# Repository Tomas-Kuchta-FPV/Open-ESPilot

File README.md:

# Open-ESPilot

This is a community-driven hardware project focused on creating an open and accessible Flight Controller (FC).   
The main focus is on being low-cost, availability, hackability and openness!  
That's why I've started this project to make an open-source and low-cost FC with the community.  

The target firmware is [ArduPilot](https://ardupilot.org/), which is a powerful open-source autopilot system.  

## Core Design Ideas
- *Dev board meets flight controller* hybrid
- Keep it budget-friendly
- Readily available components
- Hackability so you can hack on your features
- ❤️ Designed with care by and for the community

## What are the goals
The main one is a reference platform for devs and hackers. Then we can move to a product for the wider public.  

With the focus being on Hackability and Openness, there are endless possibilities for creativity!  
Here are a few ideas:
 - Prototyping and experimentation  
 - A low-cost alternative for those priced out of commercial FCs  
 - Teaching control theory and autonomous systems in schools  

## Why did I make it
I have a lot of experience with FPV drones running Betaflight.  

Then I started playing with the ESP32-based ArduPilot for almost three years. All of them were for a competition called Robotem Rovne.  
 - The first one is an autonomous rover which was breadboarded together. As with any other breadboard project, the wires were loose, they didn't make contact, and they were falling off.  
 - Then I made a second rover with an FC soldered on a proto board. Which worked wonderfully!  
 - Then I tried to make a PCB with a brushed motor controller. Not going to talk about this one. Didn't go as planned. :(  
 - After that, I've bought a SpeedyBee f405 WING FC and mounted it to an RC car. This is my Ardupilot learning platform.  

And now we are here. ...  
That was when I had the idea of making an ESP32 Flight Controller.  

## Future development
This is the first FC I made with the help of the community, so huge thanks to *everyone*. ♥️

### Ideas for future
 - modular system (eg, ELRS, GPS modules)
 - 30x30 FC for FPV drones. That's harder as there are plenty of great cheap FCs

## Project Status
**I have the PCB made, and now I need to order everything and test it!**
| PCB                                                                                                           | Render                                                                                          | Finished PCB                                                                                              |
| ------------------------------------------------------------------------------------------------------------- | ----------------------------------------------------------------------------------------------- | --------------------------------------------------------------------------------------------------------- |
|  |  |  |

### The Plan
- [x] Basic schematic and PCB layout
- [x] Selection of components is decided in [Issues](https://github.com/Tomas-Kuchta-FPV/Open-ESPilot/issues)
- [ ] Compare BOM cost to commercial FCs - going to figure it out when I have time.
- [ ] Complete code, documentation, and build guide

## Design Phases
1. **Planning & goal setting**✅
2. **Schematic design**✅
    - Start with core ESP32 + power
    - Add sensors and outputs
    - Evaluate BOM & gather feedback
3. **Community feedback loop**✅
4. **PCB layout**✅
5. **Prototype ordering**
6. **…And hopefully it works on the first try! 🤞**

## Firmware
We are now focusing on [ArduPilot ESP32 port](https://ardupilot.org/dev/docs/esp32-autopilot.html). They are making incredible work, and the project wouldn't exist without their hard work.  
I won't be able to write the code by myself, so huge props to the contributors! That's why I'm focusing on the HW.  
There are also possibilities for you to write your own code.  

## Contributing
We would love to hear feedback. We are open to everything, including issues, ideas and suggestions.  
That's why this project is Open Source.

## BOM
| Category      | Qty | Price (USD) | Description           | Link                                                                                                                                                           |
| ------------- | --- | ----------- | --------------------- | -------------------------------------------------------------------------------------------------------------------------------------------------------------- |
| PCB component | 1   | 0.9         | TMB12A05              | https://lcsc.com/product-detail/Buzzers_Huaneng-TMB12A05_C96093.html                                                                                           |
| PCB component | 14  | 0.46        | 100nF                 | https://lcsc.com/product-detail/Multilayer-Ceramic-Capacitors-MLCC-SMD-SMT_YAGEO-CC0805KRX7R9BB104_C49678.html                                                 |
| PCB component | 7   | 0.11        | 22uF                  | https://lcsc.com/product-detail/Multilayer-Ceramic-Capacitors-MLCC-SMD-SMT_Samsung-Electro-Mechanics-CL21A226MQQNNNE_C5674.html                                |
| PCB component | 1   | 0.53        | 1000uF                | https://lcsc.com/product-detail/Aluminum-Electrolytic-Capacitors-SMD_ROQANG-VT1A102M0810_C311227.html                                                          |
| PCB component | 1   | 0.57        | 1000uF (Leaded)       | https://lcsc.com/product-detail/Aluminum-Electrolytic-Capacitors-Leaded_AISHI-ERR1VM102G20OT_C398835.html                                                      |
| PCB component | 1   | 0.57        | SS34                  | https://lcsc.com/product-detail/Schottky-Diodes_MDD-Microdiode-Semiconductor-SS34_C8678.html                                                                   |
| PCB component | 2   | 0.98        | PDZVTR5.1B            | https://lcsc.com/product-detail/Zener-Diodes_ROHM-PDZVTR5-1B_C253499.html                                                                                      |
| PCB component | 1   | 0.84        | B5819W                | https://lcsc.com/product-detail/Schottky-Diodes_MDD-Microdiode-Semiconductor-B5819W_C64885.html                                                                |
| PCB component | 1   | 0.49        | WS2812B LED           | https://lcsc.com/product-detail/RGB-LEDs-Built-in-IC_XINGLIGHT-XL-5050RGBC-WS2812B_C2843785.html                                                               |
| PCB component | 1   | 0.22        | Ferrite Bead          | https://lcsc.com/product-detail/Ferrite-Beads_TDK-MPZ2012S101AT000_C15957.html                                                                                 |
| PCB component | 1   | 0.87        | USB-C Receptacle      | https://lcsc.com/product-detail/USB-Connectors_Korean-Hroparts-Elec-TYPE-C-31-M-12_C165948.html                                                                |
| PCB component | 1   | -           | MP1584 module (clone) | https://www.aliexpress.com/item/1005005870392716.html                                                                                                          |
| PCB component | 1   | -           | GY-91                 | https://www.aliexpress.com/item/32652866365.html                                                                                                               |
| PCB component | 1   | 0.6         | AO3401A               | https://lcsc.com/product-detail/MOSFETs_AOS-AO3401A_C15127.html                                                                                                |
| PCB component | 2   | 0.45        | BC847                 | https://lcsc.com/product-detail/Bipolar-BJT_Nexperia-BC847B-215_C57668.html                                                                                    |
| PCB component | 2   | 0.21        | 5.1k                  | https://lcsc.com/product-detail/Chip-Resistor-Surface-Mount_YAGEO-RC0805FR-075K1L_C84375.html                                                                  |
| PCB component | 2   | 0.19        | 10k                   | https://lcsc.com/product-detail/Chip-Resistor-Surface-Mount_YAGEO-RC0805FR-0710KL_C84376.html                                                                  |
| PCB component | 1   | 0.21        | 1k                    | https://lcsc.com/product-detail/Chip-Resistor-Surface-Mount_YAGEO-RC0805FR-075K1L_C84375.html                                                                  |
| PCB component | 5   | 0.19        | 10k                   | https://lcsc.com/product-detail/Chip-Resistor-Surface-Mount_YAGEO-RC0805FR-0710KL_C84376.html                                                                  |
| PCB component | 2   | 0.49        | 10R                   | https://lcsc.com/product-detail/Chip-Resistor-Surface-Mount_YAGEO-RC0805FR-0710RL_C96347.html                                                                  |
| PCB component | 1   | 0.41        | 0.5mΩ                 | https://lcsc.com/product-detail/Chip-Resistor-Surface-Mount_Viking-LR12FTDR0M50_C37635712.html                                                                 |
| PCB component | 4   | 0.19        | 1k                    | https://lcsc.com/product-detail/Chip-Resistor-Surface-Mount_YAGEO-RC0805FR-071KL_C95781.html                                                                   |
| PCB component | 2   | 0.63        | Push Button           | https://lcsc.com/product-detail/Tactile-Switches_ALPSALPINE-SKRKAEE020_C115357.html                                                                            |
| PCB component | 1   | 5.14        | ESP32-S3-WROOM-1-N8   | https://lcsc.com/product-detail/WiFi-Modules_ESPRESSIF-ESP32-S3-WROOM-1-N8_C2913198.html                                                                       |
| PCB component | 1   | 0.87        | AMS1117-3.3           | https://lcsc.com/product-detail/Voltage-Regulators-Linear-Low-Drop-Out-LDO-Regulators_Advanced-Monolithic-Systems-AMS1117-3-3_C6186.html                       |
| PCB component | 1   | 0.41        | AMS1117-3.3 (Alt)     | https://lcsc.com/product-detail/Voltage-Regulators-Linear-Low-Drop-Out-LDO-Regulators_Slkor-SLKORMICRO-Elec-AMS1117-3-3_C880752.html                           |
| PCB component | 1   | 2.84        | INA219                | https://lcsc.com/product-detail/Current-Sense-Amplifiers_TI-INA219AID_C1574856.html                                                                            |
| PCB component | 1   | 1.32        | Micro SD Card Slot    | https://lcsc.com/product-detail/SD-Card-Memory-Card-Connector_HRS-DM3AT-SF-PEJM5_C114218.html                                                                  |
| PCB component | 50  | 0.46        | Pin Header (5x10)     | https://lcsc.com/product-detail/Pin-Headers_BOOMELE-Boom-Precision-Elec-2-54-1-10P_C57369.html                                                                 |
| PCB component | -   | 13          | Shipping              | -                                                                                                                                                              |
| PCB           | -   | 10.72       | PCB cost              | https://cart.jlcpcb.com/quote?orderType=1&homeUploadNum=4c39875b107d460986bfa4ef1bf68f70&businessType=example&fileName=Open-ESPilot_50.6x71.1mm_for_JLCPCB.zip |
| **TOTAL**     | -   | 50.97       | -                     | -                                                                                                                                                              |

## Built With
- [ESP32](https://www.espressif.com/en/products/socs/esp32) – the core MCU
- [KiCad](https://kicad.org/) – for PCB design
- [ArduPilot](https://github.com/ArduPilot/ardupilot) – the autopilot software we're building for
- ❤️ Open source tools and community support
- ... and Love ❤️

## License
Hardware: [CERN-OHL-W](https://ohwr.org/cern_ohl_w_v2.txt)  

Firmware: Ardupilot  

## Thanks
Many thanks to the amazing people who make [Hack Club](https://hackclub.com/) possible.
Thanks to Hack Club for inspiring so many people. I don't know the numbers, but maybe around thousands.  
Most of them are probably going to get a career from it. Love your work! ❤️  

And big thanks to the ArduPilot community for keeping robotics and autonomy Open and hackable.

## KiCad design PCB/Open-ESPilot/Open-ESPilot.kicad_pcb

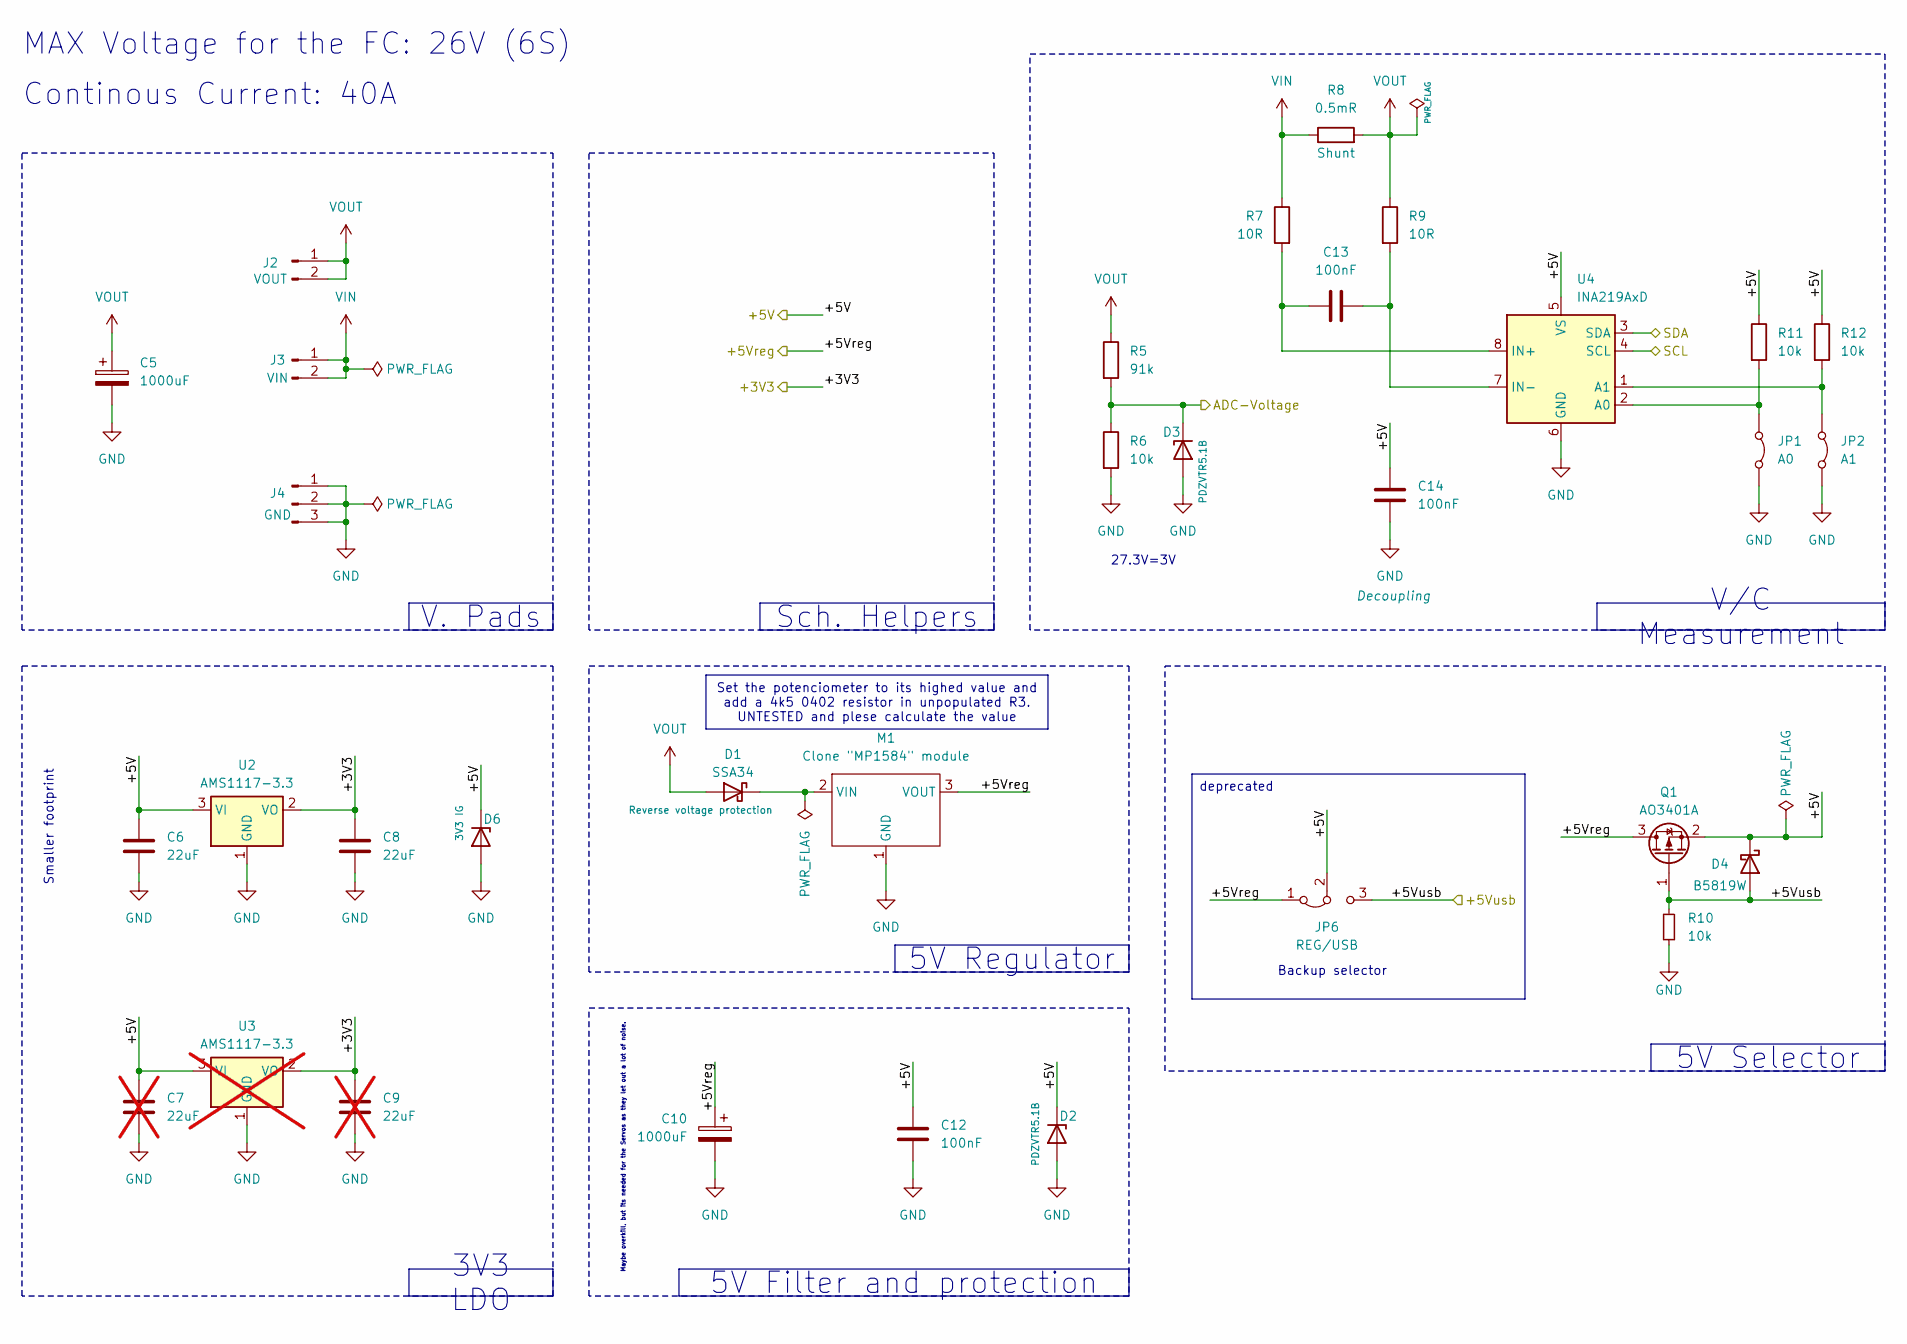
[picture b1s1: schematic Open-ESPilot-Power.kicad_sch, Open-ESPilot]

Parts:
C5: 1000uF; CP_Radial_D10.0mm_P5.00mm; LCSC C398835
C6, C8: 22uF; C_0805_2012Metric_Pad1.18x1.45mm_HandSolder; LCSC C5674
C7, C9: 22uF; C_0805_2012Metric_Pad1.18x1.45mm_HandSolder; LCSC C5674; not fitted
C10: 1000uF; CP_Elec_8x10; LCSC C311227
C12, C13, C14: 100nF; C_0805_2012Metric_Pad1.18x1.45mm_HandSolder; LCSC C49678
D1: SSA34; D_SMA; LCSC C8678
D2, D3: PDZVTR5.1B; D_SOD-128; LCSC C253499
D4: B5819W; D_SOD-123; LCSC C64885
D6: 3V3 IG; D_SOD-128
J2: VOUT; PP_02x
J3: VIN; PP_02x
J4: GND; PP_03x
JP1: A0; SolderJumper-2_P1.3mm_Bridged2Bar_RoundedPad1.0x1.5mm
JP2: A1; SolderJumper-2_P1.3mm_Bridged2Bar_RoundedPad1.0x1.5mm
JP6: REG/USB; SolderJumper-3_P1.3mm_Open_RoundedPad1.0x1.5mm
M1: Clone "MP1584" module; Clone _MP1584_ module
Q1: AO3401A; SOT-23; LCSC C15127
R5: 91k; R_0805_2012Metric_Pad1.20x1.40mm_HandSolder; LCSC C84375
R6, R10, R11, R12: 10k; R_0805_2012Metric_Pad1.20x1.40mm_HandSolder; LCSC C84376
R7, R9: 10R; R_0805_2012Metric_Pad1.20x1.40mm_HandSolder; LCSC C96347
R8: 0.5mR; R_2512_6332Metric_Pad1.40x3.35mm_HandSolder; LCSC C37635712
U2: AMS1117-3.3; SOT-89-3; LCSC C880752
U3: AMS1117-3.3; SOT-223-3_TabPin2; LCSC C6186; not fitted
U4: INA219AxD; SOIC-8_3.9x4.9mm_P1.27mm; LCSC C1574856

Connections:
+3V3: C8.1, C9.1, U2.2 (VO), U3.2 (VO); also elsewhere on the board
+5V: C6.1, C7.1, C12.1, C14.1, D2.1 (K), D4.1 (K), D6.1 (K), JP6.2 (C), Q1.2 (S), R11.1, R12.1, U2.3 (VI), U3.3 (VI), U4.5 (VS); also elsewhere on the board
+5Vreg: C10.1, JP6.1 (A), M1.3 (VOUT), Q1.3 (D); also elsewhere on the board
/Peripheral/ADC-Voltage: D3.1 (K), R5.2, R6.1; also elsewhere on the board
/Peripheral/SCL: U4.4 (SCL); also elsewhere on the board
/Peripheral/SDA: U4.3 (SDA); also elsewhere on the board
/Power/+5Vusb: D4.2 (A), JP6.3 (B), Q1.1 (G), R10.1; also elsewhere on the board
GND: C5.2, C6.2, C7.2, C8.2, C9.2, C10.2, C12.2, C14.2, D2.2 (A), D3.2 (A), D6.2 (A), J4.1, J4.2, J4.3, JP1.2 (B), JP2.2 (B), M1.1 (GND), R6.2, R10.2, U2.1 (GND), U3.1 (GND), U4.6 (GND); also elsewhere on the board
unnamed: D1.1 (K), M1.2 (VIN)
unnamed: JP1.1 (A), R11.2, U4.2 (A0)
unnamed: JP2.1 (A), R12.2, U4.1 (A1)
unnamed: C13.1, R7.2, U4.8 (IN+)
unnamed: C13.2, R9.2, U4.7 (IN-)
VIN: J3.1, J3.2, R7.1, R8.1
VOUT: C5.1, D1.2 (A), J2.1, J2.2, R5.1, R8.2, R9.1

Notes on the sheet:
Smaller footprint
MAX Voltage for the FC: 26V (6S)
Continous Current: 40A
Backup selector
Maybe overkill, but its needed for the Servos as they let out a lot of noise.
27.3V=3V
V. Pads
5V Regulator
Sch. Helpers
deprecated
3V3 LDO
V/C Measurement
5V Filter and protection
Set the potenciometer to its highed value and add a 4k5 0402 resistor in unpopulated R3. UNTESTED and plese calculate the value
5V Selector

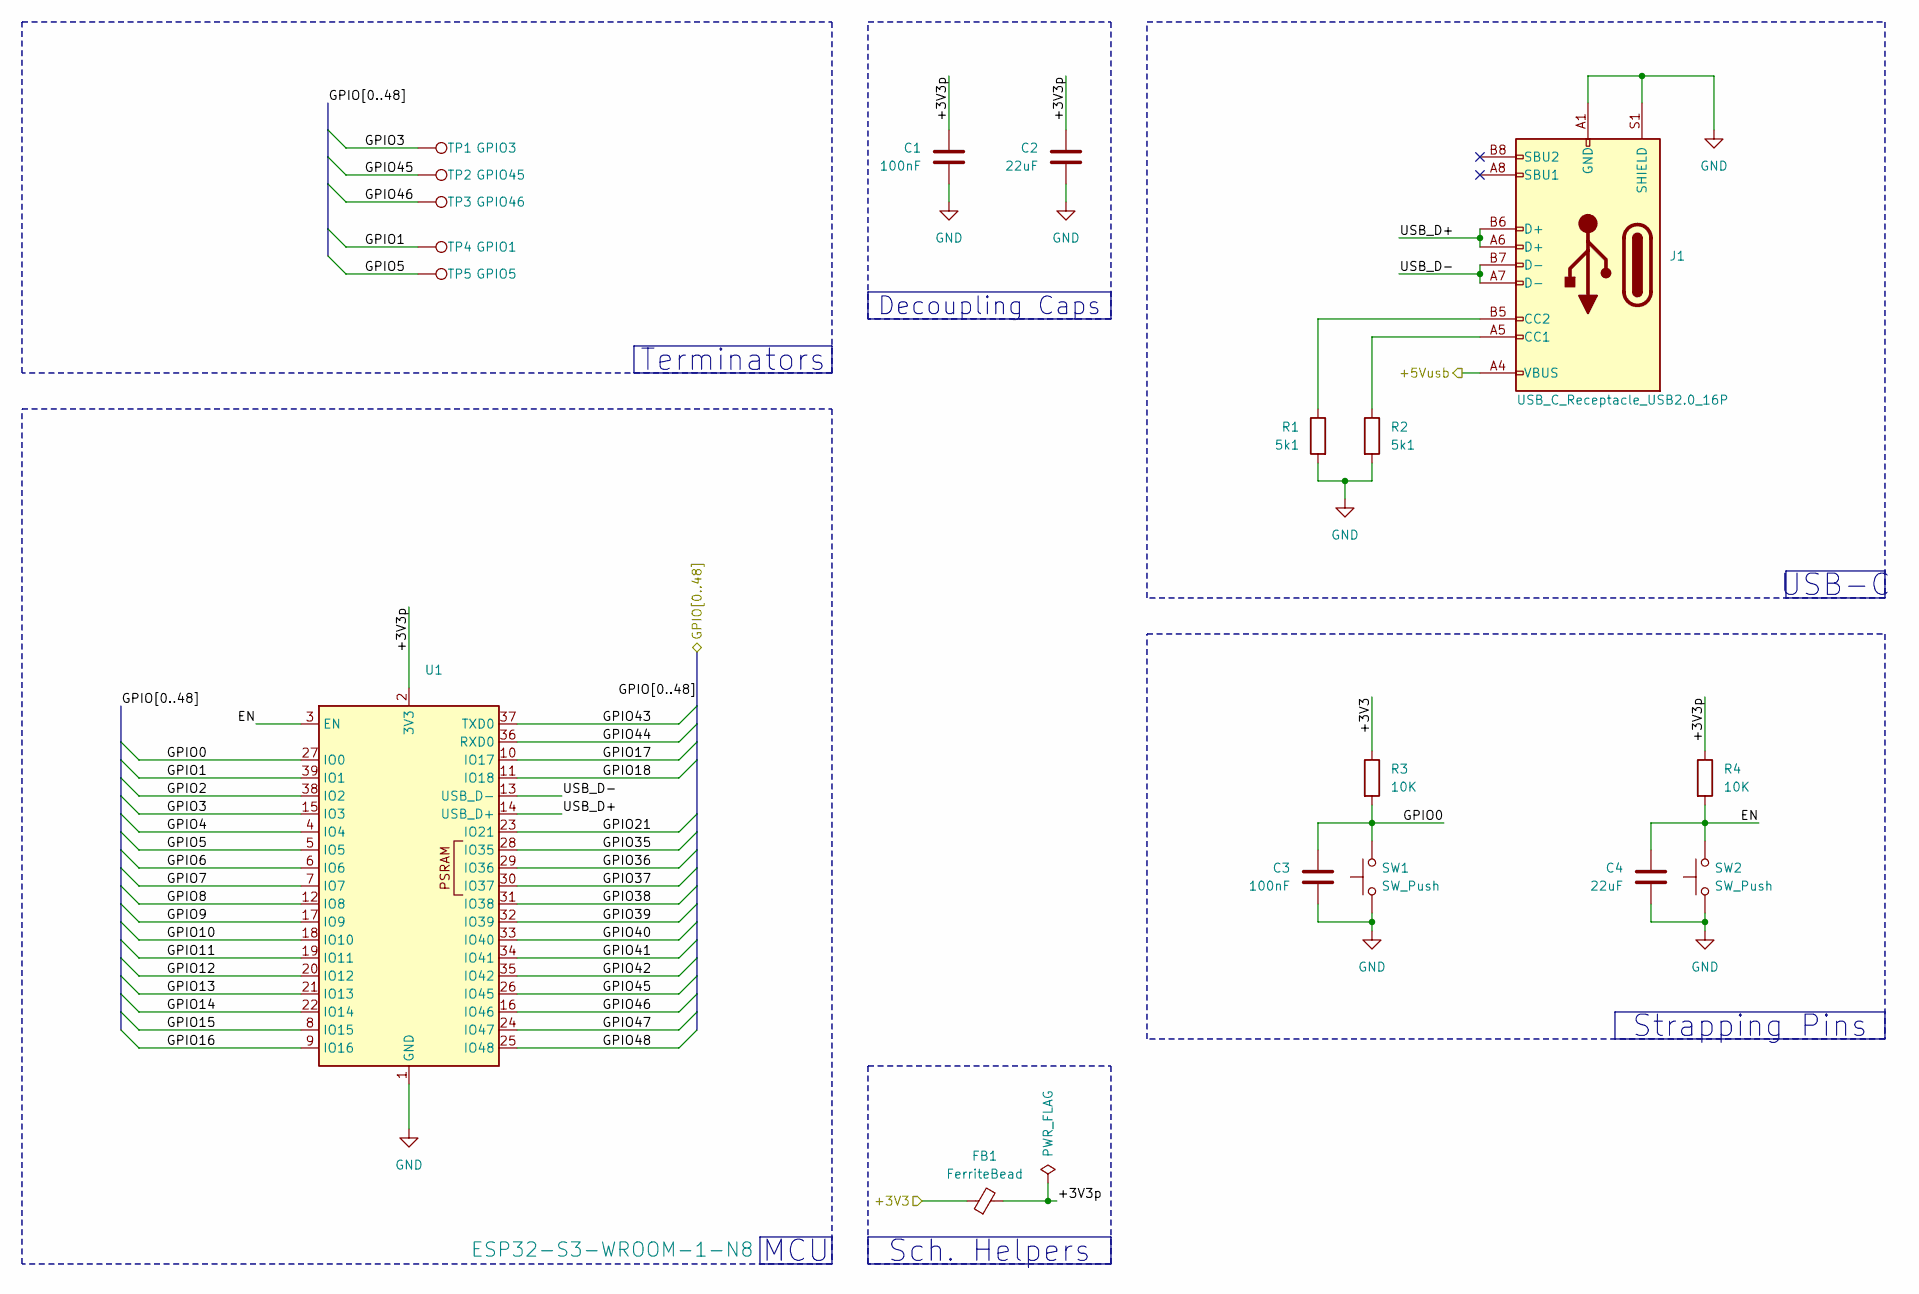
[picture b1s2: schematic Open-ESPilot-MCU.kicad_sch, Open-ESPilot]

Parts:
C1, C3: 100nF; C_0805_2012Metric_Pad1.18x1.45mm_HandSolder; LCSC C49678
C2, C4: 22uF; C_0805_2012Metric_Pad1.18x1.45mm_HandSolder; LCSC C5674
FB1: FerriteBead; L_0805_2012Metric_Pad1.05x1.20mm_HandSolder; LCSC C15957
J1: USB_C_Receptacle_USB2.0_16P; USB_C_Receptacle_HRO_TYPE-C-31-M-12; LCSC C165948
R1, R2: 5k1; R_0805_2012Metric_Pad1.20x1.40mm_HandSolder; LCSC C84375
R3, R4: 10K; R_0805_2012Metric_Pad1.20x1.40mm_HandSolder; LCSC C84376
SW1, SW2: SW_Push; SW_Push_SPST_NO_Alps_SKRK; LCSC C115357
TP1: GPIO3; TestPoint_Pad_D2.0mm
TP2: GPIO45; TestPoint_Pad_D2.0mm
TP3: GPIO46; TestPoint_Pad_D2.0mm
TP4: GPIO1; TestPoint_THTPad_D2.0mm_Drill1.0mm
TP5: GPIO5; TestPoint_Pad_D2.0mm
U1: ESP32-S3-WROOM-1-N8; ESP32-S3-WROOM-1; LCSC C2913198

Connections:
+3V3: FB1.1, R3.1; also elsewhere on the board
/MCU/+3V3p: C1.1, C2.1, FB1.2, R4.1, U1.2 (3V3)
/MCU/EN: C4.1, R4.2, SW2.2, U1.3 (EN)
/MCU/GPIO0: C3.1, R3.2, SW1.2, U1.27 (IO0)
/MCU/GPIO1: TP4.1, U1.39 (IO1)
/MCU/GPIO2: U1.38 (IO2); also elsewhere on the board
/MCU/GPIO3: TP1.1, U1.15 (IO3)
/MCU/GPIO4: U1.4 (IO4); also elsewhere on the board
/MCU/GPIO5: TP5.1, U1.5 (IO5)
/MCU/GPIO6: U1.6 (IO6); also elsewhere on the board
/MCU/GPIO7: U1.7 (IO7); also elsewhere on the board
/MCU/GPIO8: U1.12 (IO8); also elsewhere on the board
/MCU/GPIO9: U1.17 (IO9); also elsewhere on the board
/MCU/GPIO10: U1.18 (IO10); also elsewhere on the board
/MCU/GPIO11: U1.19 (IO11); also elsewhere on the board
/MCU/GPIO12: U1.20 (IO12); also elsewhere on the board
/MCU/GPIO13: U1.21 (IO13); also elsewhere on the board
/MCU/GPIO14: U1.22 (IO14); also elsewhere on the board
/MCU/GPIO15: U1.8 (IO15); also elsewhere on the board
/MCU/GPIO16: U1.9 (IO16); also elsewhere on the board
/MCU/GPIO17: U1.10 (IO17); also elsewhere on the board
/MCU/GPIO18: U1.11 (IO18); also elsewhere on the board
/MCU/GPIO21: U1.23 (IO21); also elsewhere on the board
/MCU/GPIO35: U1.28 (IO35); also elsewhere on the board
/MCU/GPIO36: U1.29 (IO36); also elsewhere on the board
/MCU/GPIO37: U1.30 (IO37); also elsewhere on the board
/MCU/GPIO38: U1.31 (IO38); also elsewhere on the board
/MCU/GPIO39: U1.32 (IO39); also elsewhere on the board
/MCU/GPIO40: U1.33 (IO40); also elsewhere on the board
/MCU/GPIO41: U1.34 (IO41); also elsewhere on the board
/MCU/GPIO42: U1.35 (IO42); also elsewhere on the board
/MCU/GPIO43: U1.37 (TXD0); also elsewhere on the board
/MCU/GPIO44: U1.36 (RXD0); also elsewhere on the board
/MCU/GPIO45: TP2.1, U1.26 (IO45)
/MCU/GPIO46: TP3.1, U1.16 (IO46)
/MCU/GPIO47: U1.24 (IO47); also elsewhere on the board
/MCU/GPIO48: U1.25 (IO48); also elsewhere on the board
/MCU/USB_D+: J1.A6 (D+), J1.B6 (D+), U1.14 (USB_D+)
/MCU/USB_D-: J1.A7 (D-), J1.B7 (D-), U1.13 (USB_D-)
/Power/+5Vusb: J1.A4 (VBUS), J1.A9 (VBUS), J1.B4 (VBUS), J1.B9 (VBUS); also elsewhere on the board
GND: C1.2, C2.2, C3.2, C4.2, J1.A1 (GND), J1.A12 (GND), J1.B1 (GND), J1.B12 (GND), J1.S1 (SHIELD), R1.2, R2.2, SW1.1, SW2.1, U1.1 (GND), U1.40 (GND), U1.41 (GND); also elsewhere on the board
unnamed: J1.A5 (CC1), R2.1
unnamed: J1.B5 (CC2), R1.1

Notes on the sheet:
USB-C
Strapping Pins
Terminators
Sch. Helpers
MCU
Decoupling Caps

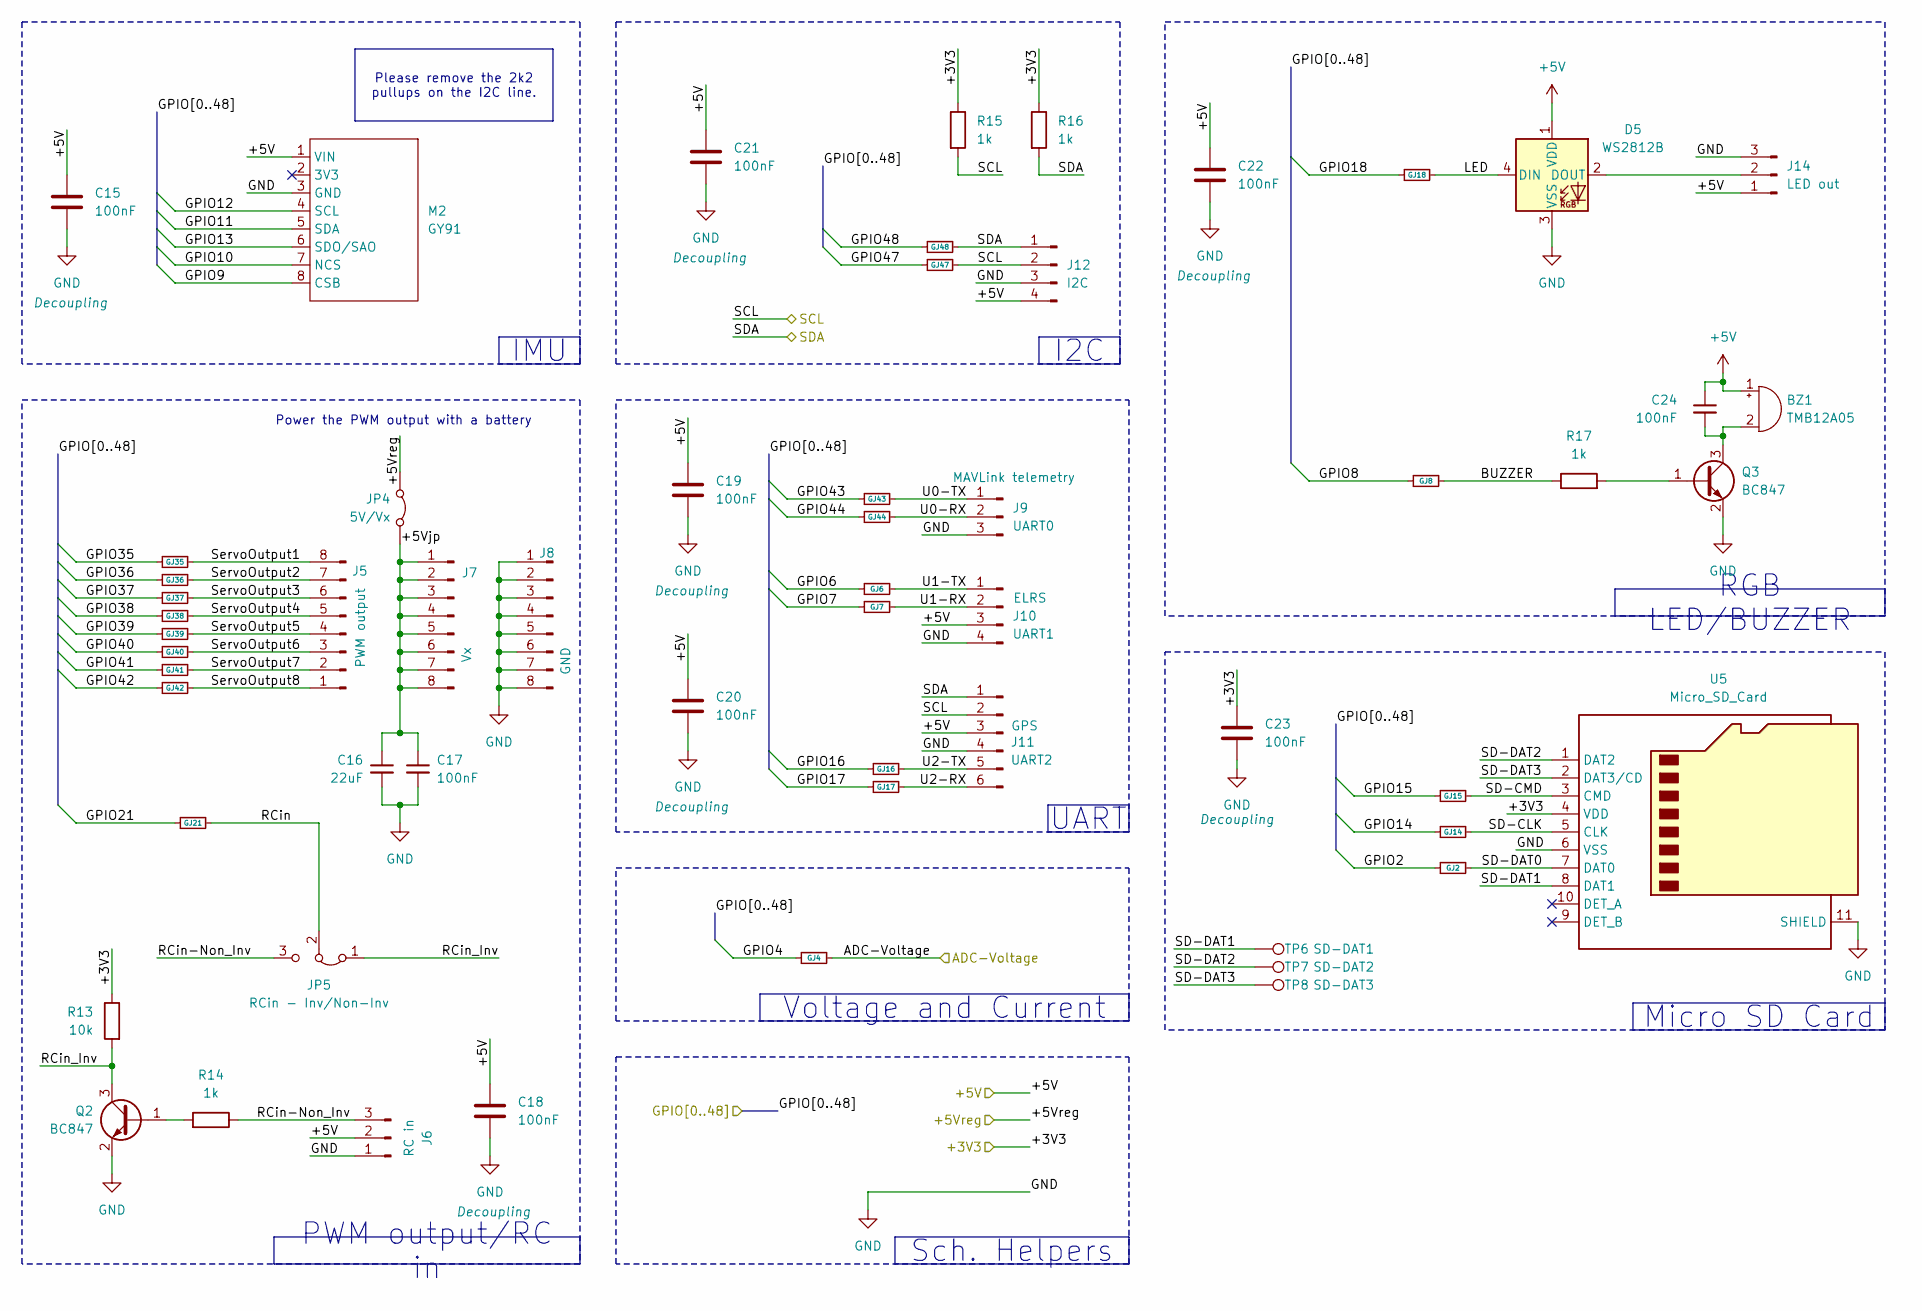
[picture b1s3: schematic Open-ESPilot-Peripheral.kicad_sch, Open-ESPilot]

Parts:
BZ1: TMB12A05; Buzzer_12x9.5RM7.6; LCSC C96093
C15, C17, C18, C19, C20, C21, C22, C23, C24: 100nF; C_0805_2012Metric_Pad1.18x1.45mm_HandSolder; LCSC C49678
C16: 22uF; C_0805_2012Metric_Pad1.18x1.45mm_HandSolder; LCSC C5674
D5: WS2812B; LED_WS2812B_PLCC4_5.0x5.0mm_P3.2mm; LCSC C2843785
GJ2, GJ4, GJ6, GJ7, GJ8, GJ14, GJ15, GJ16, GJ17, GJ18, GJ21, GJ35, GJ36, GJ37, GJ38, GJ39, GJ40, GJ41, GJ42, GJ43, GJ44, GJ47, GJ48: R_Small; SolderJumper-2_P1.3mm_Bridged2Bar_RoundedPad1.0x1.5mm
J5: PWM output; PinHeader_1x08_P2.54mm_Vertical
J6: RC in; PinHeader_1x03_P2.54mm_Vertical
J7: Vx; PinHeader_1x08_P2.54mm_Vertical
J8: GND; PinHeader_1x08_P2.54mm_Vertical
J9: UART0; PinHeader_1x03_P2.54mm_Vertical
J10: UART1; PinHeader_1x04_P2.54mm_Vertical
J11: UART2; PinHeader_1x06_P2.54mm_Vertical
J12: I2C; PinHeader_1x04_P2.54mm_Vertical
J14: LED out; PinHeader_1x03_P2.54mm_Vertical
JP4: 5V/Vx; SolderJumper-2_P1.3mm_Bridged2Bar_RoundedPad1.0x1.5mm
JP5: RCin - Inv/Non-Inv; SolderJumper-3_P1.3mm_Bridged2Bar12_RoundedPad1.0x1.5mm_Num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
M2: GY91; GY-91
Q2, Q3: BC847; SOT-23; LCSC C57668
R13: 10k; R_0805_2012Metric_Pad1.20x1.40mm_HandSolder; LCSC C84376
R14, R15, R16, R17: 1k; R_0805_2012Metric_Pad1.20x1.40mm_HandSolder; LCSC C95781
TP6: SD-DAT1; TestPoint_Pad_D2.0mm
TP7: SD-DAT2; TestPoint_Pad_D2.0mm
TP8: SD-DAT3; TestPoint_Pad_D2.0mm
U5: Micro_SD_Card; microSD_HC_Hirose_DM3AT-SF-PEJM5; LCSC C114218

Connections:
+3V3: C23.1, R13.1, R15.1, R16.1, U5.4 (VDD); also elsewhere on the board
+5V: BZ1.1 (+), C15.1, C18.1, C19.1, C20.1, C21.1, C22.1, C24.1, D5.1 (VDD), J6.2, J10.3, J11.3, J12.4, J14.1, M2.1 (VIN); also elsewhere on the board
+5Vreg: JP4.2 (B); also elsewhere on the board
/MCU/GPIO2: GJ2.2; also elsewhere on the board
/MCU/GPIO4: GJ4.2; also elsewhere on the board
/MCU/GPIO6: GJ6.2; also elsewhere on the board
/MCU/GPIO7: GJ7.2; also elsewhere on the board
/MCU/GPIO8: GJ8.2; also elsewhere on the board
/MCU/GPIO9: M2.8 (CSB); also elsewhere on the board
/MCU/GPIO10: M2.7 (NCS); also elsewhere on the board
/MCU/GPIO11: M2.5 (SDA); also elsewhere on the board
/MCU/GPIO12: M2.4 (SCL); also elsewhere on the board
/MCU/GPIO13: M2.6 (SDO/SAO); also elsewhere on the board
/MCU/GPIO14: GJ14.2; also elsewhere on the board
/MCU/GPIO15: GJ15.2; also elsewhere on the board
/MCU/GPIO16: GJ16.2; also elsewhere on the board
/MCU/GPIO17: GJ17.2; also elsewhere on the board
/MCU/GPIO18: GJ18.2; also elsewhere on the board
/MCU/GPIO21: GJ21.2; also elsewhere on the board
/MCU/GPIO35: GJ35.2; also elsewhere on the board
/MCU/GPIO36: GJ36.2; also elsewhere on the board
/MCU/GPIO37: GJ37.2; also elsewhere on the board
/MCU/GPIO38: GJ38.2; also elsewhere on the board
/MCU/GPIO39: GJ39.2; also elsewhere on the board
/MCU/GPIO40: GJ40.2; also elsewhere on the board
/MCU/GPIO41: GJ41.2; also elsewhere on the board
/MCU/GPIO42: GJ42.2; also elsewhere on the board
/MCU/GPIO43: GJ43.2; also elsewhere on the board
/MCU/GPIO44: GJ44.2; also elsewhere on the board
/MCU/GPIO47: GJ47.2; also elsewhere on the board
/MCU/GPIO48: GJ48.2; also elsewhere on the board
/Peripheral/+5Vjp: C16.1, C17.1, J7.1, J7.2, J7.3, J7.4, J7.5, J7.6, J7.7, J7.8, JP4.1 (A)
/Peripheral/ADC-Voltage: GJ4.1; also elsewhere on the board
/Peripheral/BUZZER: GJ8.1, R17.1
/Peripheral/LED: D5.4 (DIN), GJ18.1
/Peripheral/RCin: GJ21.1, JP5.2 (C)
/Peripheral/RCin-Non_Inv: J6.3, JP5.3 (B), R14.1
/Peripheral/RCin_Inv: JP5.1 (A), Q2.3 (C), R13.2
/Peripheral/SCL: GJ47.1, J11.2, J12.2, R15.2; also elsewhere on the board
/Peripheral/SD-CLK: GJ14.1, U5.5 (CLK)
/Peripheral/SD-CMD: GJ15.1, U5.3 (CMD)
/Peripheral/SD-DAT0: GJ2.1, U5.7 (DAT0)
/Peripheral/SD-DAT1: TP6.1, U5.8 (DAT1)
/Peripheral/SD-DAT2: TP7.1, U5.1 (DAT2)
/Peripheral/SD-DAT3: TP8.1, U5.2 (DAT3/CD)
/Peripheral/SDA: GJ48.1, J11.1, J12.1, R16.2; also elsewhere on the board
/Peripheral/ServoOutput1: GJ35.1, J5.8
/Peripheral/ServoOutput2: GJ36.1, J5.7
/Peripheral/ServoOutput3: GJ37.1, J5.6
/Peripheral/ServoOutput4: GJ38.1, J5.5
/Peripheral/ServoOutput5: GJ39.1, J5.4
/Peripheral/ServoOutput6: GJ40.1, J5.3
/Peripheral/ServoOutput7: GJ41.1, J5.2
/Peripheral/ServoOutput8: GJ42.1, J5.1
/Peripheral/U0-RX: GJ44.1, J9.2
/Peripheral/U0-TX: GJ43.1, J9.1
/Peripheral/U1-RX: GJ7.1, J10.2
/Peripheral/U1-TX: GJ6.1, J10.1
/Peripheral/U2-RX: GJ17.1, J11.6
/Peripheral/U2-TX: GJ16.1, J11.5
GND: C15.2, C16.2, C17.2, C18.2, C19.2, C20.2, C21.2, C22.2, C23.2, D5.3 (VSS), J6.1, J8.1, J8.2, J8.3, J8.4, J8.5, J8.6, J8.7, J8.8, J9.3, J10.4, J11.4, J12.3, J14.3, M2.3 (GND), Q2.2 (E), Q3.2 (E), U5.6 (VSS), U5.11 (SHIELD); also elsewhere on the board
unnamed: BZ1.2 (-), C24.2, Q3.3 (C)
unnamed: D5.2 (DOUT), J14.2
unnamed: Q2.1 (B), R14.2
unnamed: Q3.1 (B), R17.2

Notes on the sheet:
Power the PWM output with a battery
Micro SD Card
Voltage and Current
RGB LED/BUZZER
Sch. Helpers
IMU
I2C
UART
Please remove the 2k2 pullups on the I2C line.
PWM output/RC in

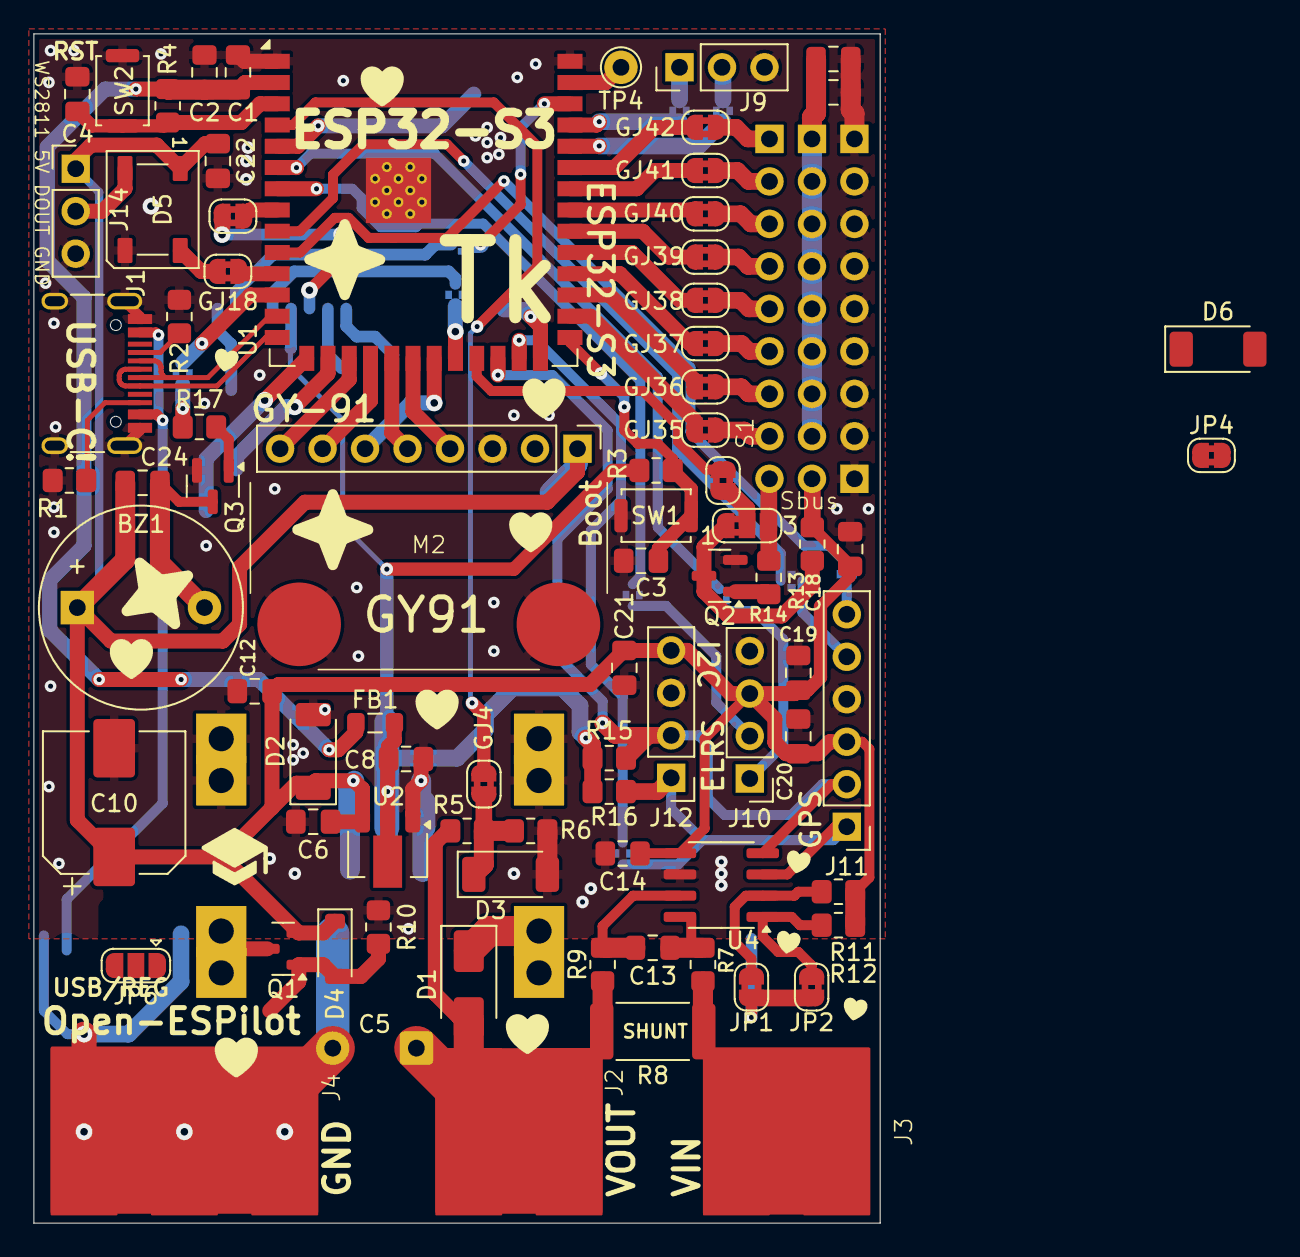
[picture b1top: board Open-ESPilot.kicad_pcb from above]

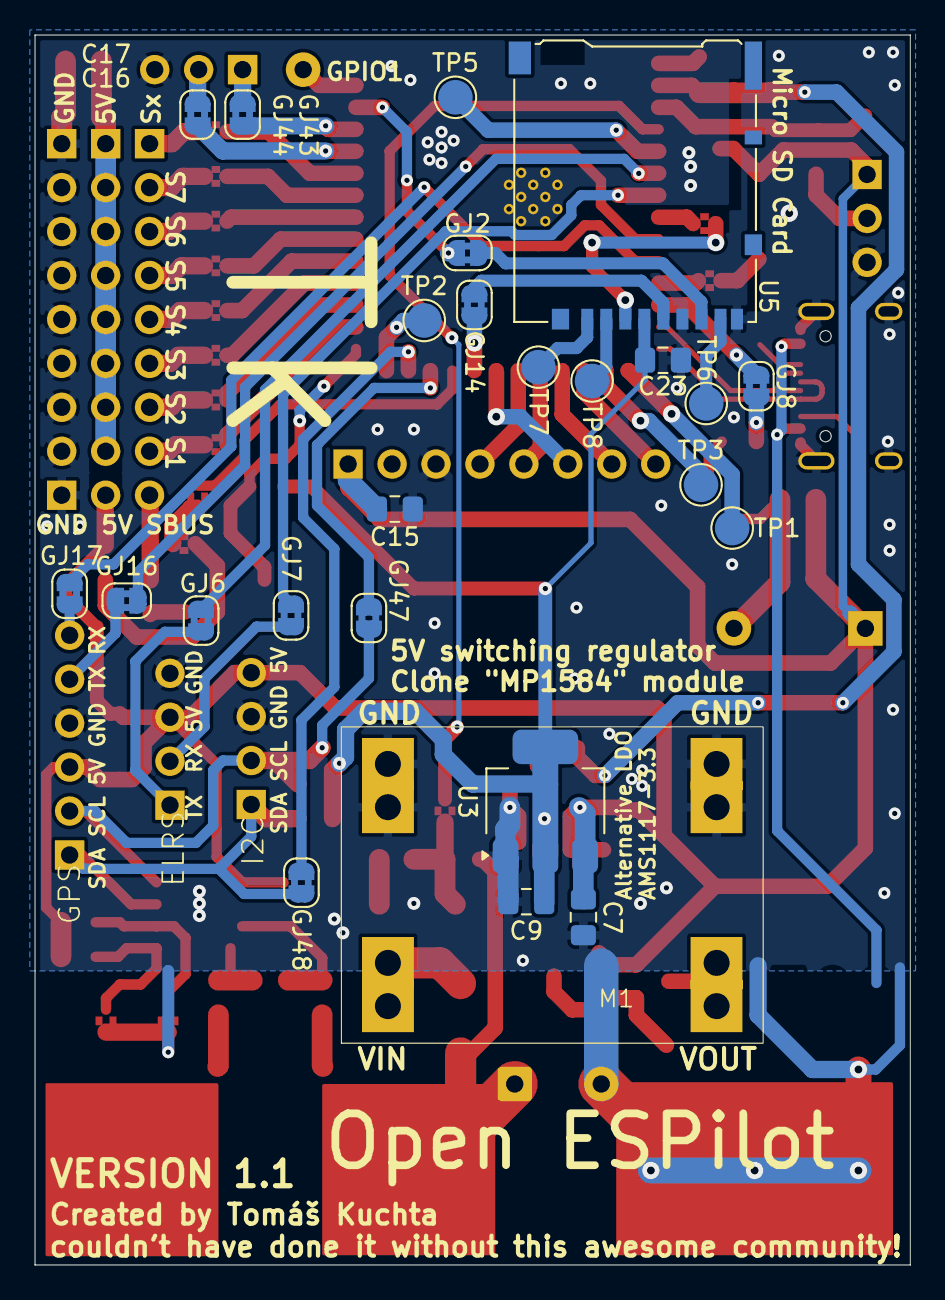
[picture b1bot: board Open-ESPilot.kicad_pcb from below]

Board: 2 copper layers, 50.6 x 71.1 mm, 109 parts (25 on the bottom side), 85 nets.

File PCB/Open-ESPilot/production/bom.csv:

Designator,Footprint,Quantity,Value,LCSC Part #
BZ1,Buzzer_12x9.5RM7.6,1,TMB12A05,C96093
"C1, C12, C13, C14, C15, C17, C18, C19, C20, C21, C22, C23, C24, C3",0805,14,100nF,
C10,CP_Elec_8x10,1,1000uF,C311227
"C16, C4, C6, C8",0805,4,22uF,
C2,0805,1,22uF,C5674
C5,CP_Radial_D10.0mm_P5.00mm,1,1000uF,C398835
D1,D_SMA,1,SSA34,C8678
"D2, D3",D_SOD-128,2,PDZVTR5.1B,C253499
D4,D_SOD-123,1,B5819W,C64885
D5,LED_WS2812B_PLCC4_5.0x5.0mm_P3.2mm,1,WS2812B,
FB1,0805,1,FerriteBead,C15957
J1,USB_C_Receptacle_HRO_TYPE-C-31-M-12,1,USB_C_Receptacle_USB2.0_16P,C165948
J10,PinHeader_1x04_P2.54mm_Vertical,1,UART1,
J11,PinHeader_1x06_P2.54mm_Vertical,1,UART2,
J12,PinHeader_1x04_P2.54mm_Vertical,1,I2C,
J14,PinHeader_1x03_P2.54mm_Vertical,1,LED out,
J2,PP_02x,1,VOUT,
J3,PP_02x,1,VIN,
J4,PP_03x,1,GND,
J5,PinHeader_1x08_P2.54mm_Vertical,1,PWM output,
J6,PinHeader_1x03_P2.54mm_Vertical,1,RC in,
J7,PinHeader_1x08_P2.54mm_Vertical,1,Vx,
J8,PinHeader_1x08_P2.54mm_Vertical,1,GND,
J9,PinHeader_1x03_P2.54mm_Vertical,1,UART0,
"JP10, JP11, JP12, JP15, JP16, JP17, JP18, JP19, JP20, JP21, JP22, JP23, JP24, JP25, JP26, JP27, JP28, JP4, JP5, JP6, JP7, JP8, JP9",SolderJumper-2_P1.3mm_Bridged2Bar_RoundedPad1.0x1.5mm,23,R_Small,
JP14,SolderJumper-2_P1.3mm_Bridged2Bar_RoundedPad1.0x1.5mm,1,5V/Vx,
JP2,SolderJumper-2_P1.3mm_Bridged2Bar_RoundedPad1.0x1.5mm,1,A0,
JP3,SolderJumper-2_P1.3mm_Bridged2Bar_RoundedPad1.0x1.5mm,1,A1,
M1,Clone _MP1584_ module,1,"Clone ""MP1584"" module",
M2,GY-91,1,GY91,
Q1,SOT-23,1,AO3401A,C15127
"Q2, Q3",SOT-23,2,BC847,C57668
"R1, R2",0805,2,5k1,
"R10, R11, R12, R13, R3, R4, R6",0805,7,10k,
"R14, R15, R16, R17",0805,4,1k,
R5,0805,1,91k,
"R7, R9",0805,2,10R,
R8,2512,1,0.5mR,C37635712
"SW1, SW2",SW_Push_SPST_NO_Alps_SKRK,2,SW_Push,C115357
TP1,TestPoint_Pad_D2.0mm,1,GPIO3,
TP2,TestPoint_Pad_D2.0mm,1,GPIO45,
TP3,TestPoint_Pad_D2.0mm,1,GPIO46,
TP4,TestPoint_THTPad_D2.0mm_Drill1.0mm,1,GPIO1,
TP5,TestPoint_Pad_D2.0mm,1,GPIO5,
TP6,TestPoint_Pad_D2.0mm,1,SD-DAT1,
TP7,TestPoint_Pad_D2.0mm,1,SD-DAT2,
TP8,TestPoint_Pad_D2.0mm,1,SD-DAT3,
U1,ESP32-S3-WROOM-1,1,ESP32-S3-WROOM-1-N8,
U2,SOT-89-3,1,AMS1117-3.3,C880752
U4,SOIC-8_3.9x4.9mm_P1.27mm,1,INA219AxD,
U5,microSD_HC_Hirose_DM3AT-SF-PEJM5,1,Micro_SD_Card,C114218

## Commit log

2025-06-21 Add initial project files: JOURNAL, LICENSE, and README
2025-06-26 made goals clearer Component selection
2025-06-28 Added basic unfinished schematic for esp32s3 and Pin definitions.
2025-06-29 Added Journal entry and Edited readme.
2025-06-30 Finished schematic for the ESP32S3.
2025-06-30 Worked on the Power Schematic. Added voltage input and a switching regulator. Fixed the LDO.
2025-06-30 Edited Power schematic and insted of the IC I have decided to use modules.
2025-06-30 Added another Journal entry from this day.
2025-06-30 The images didnt work propperly hopefully they will work now
2025-06-30 journal didnt save
2025-06-30 now?!
2025-06-30 Added timestamps.
2025-07-01 Edited the MP1584 module and added Schematic and footprint of the GY-91 and implemented it to the schematic.
2025-07-01 New journal entry.
2025-07-01 Added Libre Office to .gitignore.
2025-07-04 Fixed the extension of license to md and edited readme to be more readable.
2025-07-08 IMU not INS
2025-07-08 Decided on Pin Assigment
2025-07-08 New Jornal entry
2025-07-08 journal fixes.
2025-07-08 Added a message to let know there can be some issues with my english.
2025-07-10 Journal fixes
2025-07-16 Edited Pin definitions to Open ESPilot. And added the pheripherials to the schematic. Also new journal entry.
2025-07-16 Journal and Schematic fixes.
2025-07-17 Schematic Fixes
2025-07-17 more Schematic fixes yay
2025-07-19 Fixed spacing.
2025-07-19 Assigned footprints and components for the easy ones (R,C,JP,J)
2025-07-21 rearenged pins and moved polyfuse.
2025-07-24 Added new footprints for power pads and added decoupling capacitors.
2025-07-24 Completed the INA219 current sensor schematic. Changed the I2C pullups for a value thats common on board.
2025-07-24 Adjusted the Power schematic.
2025-07-24 Added Ferite bead for the ESP.
2025-07-24 Deleted the h. 😅
2025-07-24 Reanotated Schematic.
2025-07-24 Decided on voltage divider.
2025-07-24 PCB init.
2025-07-25 Started routing. I have few things there. Fixed schematic.
2025-07-27 halve of the PCB is routed.
2025-07-29 I'm rushing it! :( Finished the PCB
2025-07-30 Added labels to headers.
2025-07-30 New journal entrys.
2025-07-30 README updated.
2025-07-30 Selected componets and tried to made a csv.
2025-07-30 Readme fix
2025-07-30 BOM fix
2025-08-02 Fixed a BOM oversight.
2025-08-03 Rewrite of the README without the help of AI.
2025-08-03 Forgor the Thanks.
2025-08-03 Fixed typos.
2025-08-06 moved BOM.
2025-09-13 Preparing to order
2025-09-22 Removed paste layer for PPs and GY-91
2025-09-22 Odering and some issues.
2025-09-22 MOved BOM back to /PCB
2025-09-22 Modified gitignore
2025-10-28 Finished the PCB. And a new Journal entry.
2026-04-05 added build blog for take two
2026-04-05 Document issues and improvements for blog build
    Added detailed notes on issues encountered during the blog build process, including troubleshooting steps and a list of improvements needed.
2026-05-13 in dabenginging of V1.1
2026-05-13 PCB init of V1.1
